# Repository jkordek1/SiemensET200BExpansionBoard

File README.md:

# SiemensET200BExpansionBoard

## Description
PCB expansion device containing 16 SPDT switches for configuring Siemens ET200B.
## Images

## BOM
| #  | QTY | Component | Link
| ------------- | ------------- | ------------- | ------------- |
| 1  | 16 | EG1271A SPDT switch  | [Digikey](https://www.digikey.com/en/products/detail/e-switch/EG1271A/251336) |
| 2  | 1 | 5.08mm 1x2 screw terminal  | [Digikey](https://www.digikey.com/en/products/detail/cui-devices/TB006-508-02BE/10064115) |

## Project folder structure
    .
    ├── ...
    ├── Images                  # Images of the project
    ├── KiCAD Files             # Main folder
    │   ├── 3D                  # 3D models of added components
    │   ├── Images              # Graphics added to silk
    │   └── jlcpcb              # gerber and assembly folder - addon
    └── ...

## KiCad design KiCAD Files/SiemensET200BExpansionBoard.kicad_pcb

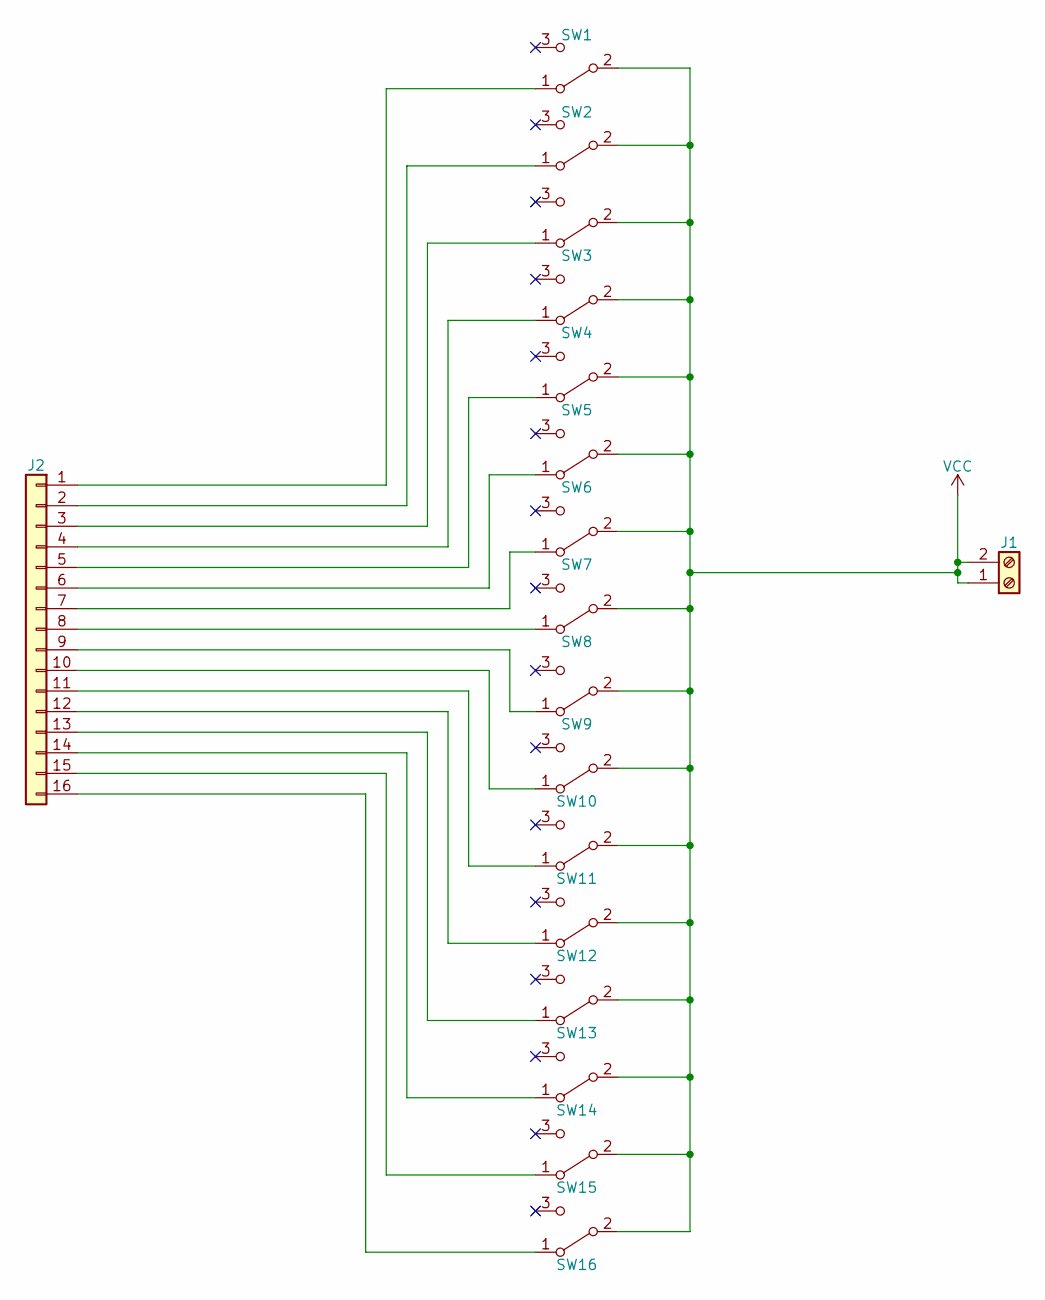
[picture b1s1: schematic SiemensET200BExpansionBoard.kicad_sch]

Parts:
J1: Screw_Terminal_01x02; TerminalBlock_Phoenix_MKDS-1,5-2-5.08_1x02_P5.08mm_Horizont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
J2: Conn_01x16; Konektor
SW1, SW2, SW3, SW4, SW5, SW6, SW7, SW8, SW9, SW10, SW11, SW12, SW13, SW14, SW15, SW16: SW_SPDT; EG1271A

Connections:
unnamed: J2.1, SW1.1 (A)
unnamed: J2.2, SW2.1 (A)
unnamed: J2.3, SW3.1 (A)
unnamed: J2.4, SW4.1 (A)
unnamed: J2.5, SW5.1 (A)
unnamed: J2.6, SW6.1 (A)
unnamed: J2.7, SW7.1 (A)
unnamed: J2.8, SW8.1 (A)
unnamed: J2.9, SW9.1 (A)
unnamed: J2.10, SW10.1 (A)
unnamed: J2.11, SW11.1 (A)
unnamed: J2.12, SW12.1 (A)
unnamed: J2.13, SW13.1 (A)
unnamed: J2.14, SW14.1 (A)
unnamed: J2.15, SW15.1 (A)
unnamed: J2.16, SW16.1 (A)
VCC: J1.1, J1.2, SW1.2 (B), SW2.2 (B), SW3.2 (B), SW4.2 (B), SW5.2 (B), SW6.2 (B), SW7.2 (B), SW8.2 (B), SW9.2 (B), SW10.2 (B), SW11.2 (B), SW12.2 (B), SW13.2 (B), SW14.2 (B), SW15.2 (B), SW16.2 (B)

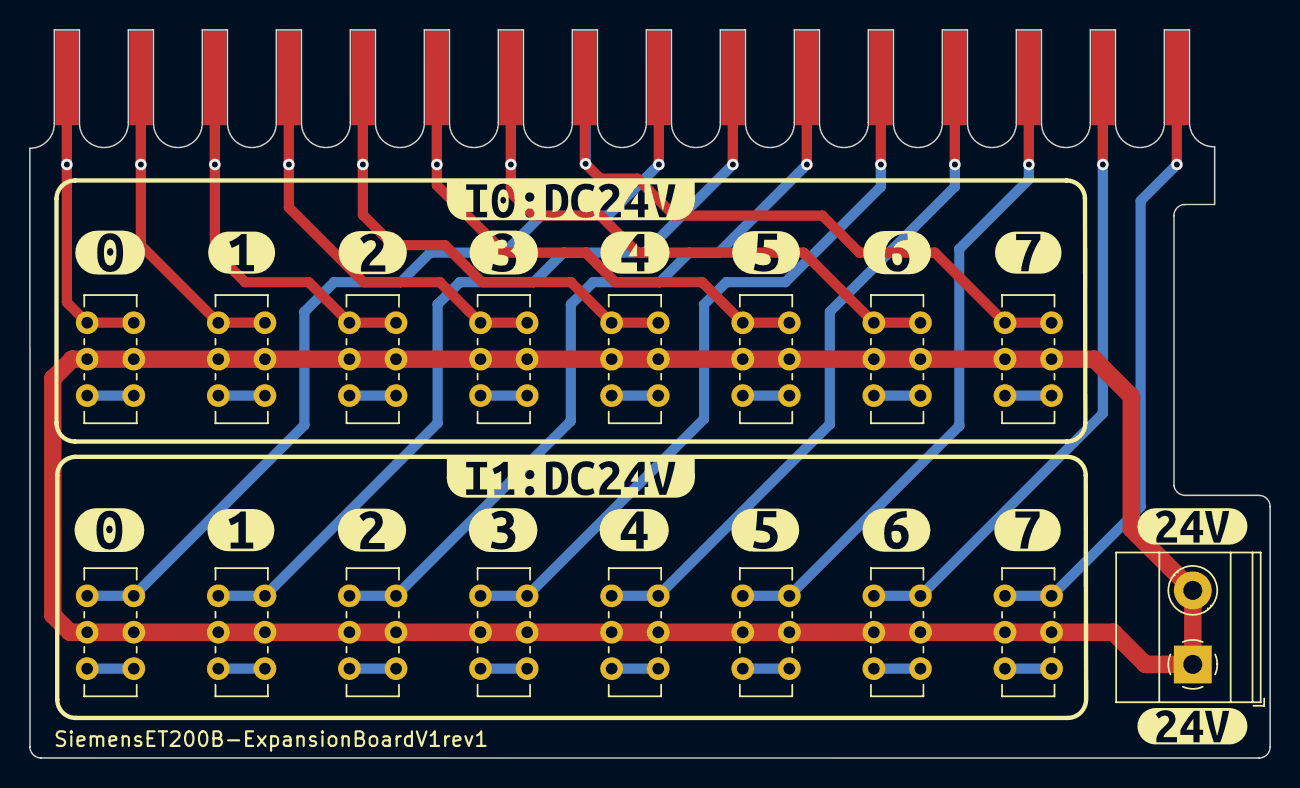
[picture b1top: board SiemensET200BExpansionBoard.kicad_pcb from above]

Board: 2 copper layers, 85.1 x 50.0 mm, 38 parts (0 on the bottom side), 17 nets.

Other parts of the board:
kibuzzard-63C10C4F, kibuzzard-63C10C4F#2: G***; kibuzzard-63C10C4F
kibuzzard-63C11BDD: G***; kibuzzard-63C11BDD
kibuzzard-63C11C3D: G***; kibuzzard-63C11C3D
kibuzzard-63C11C89, kibuzzard-63C11C89#2: G***; kibuzzard-63C11C89
kibuzzard-63C11C98, kibuzzard-63C11C98#2: G***; kibuzzard-63C11C98
kibuzzard-63C11CB4, kibuzzard-63C11CB4#2: G***; kibuzzard-63C11CB4
kibuzzard-63C11CBB, kibuzzard-63C11CBB#2: G***; kibuzzard-63C11CBB
kibuzzard-63C11CC1, kibuzzard-63C11CC1#2: G***; kibuzzard-63C11CC1
kibuzzard-63C11CC9, kibuzzard-63C11CC9#2: G***; kibuzzard-63C11CC9
kibuzzard-63C11CDA, kibuzzard-63C11CDA#2: G***; kibuzzard-63C11CDA
kibuzzard-63C11CE2, kibuzzard-63C11CE2#2: G***; kibuzzard-63C11CE2

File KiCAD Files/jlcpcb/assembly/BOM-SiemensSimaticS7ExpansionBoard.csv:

Comment,Designator,Footprint,LCSC
SW_SPDT,SW16,EG1271A,
SW_SPDT,SW15,EG1271A,
SW_SPDT,SW14,EG1271A,
SW_SPDT,SW13,EG1271A,
SW_SPDT,SW12,EG1271A,
SW_SPDT,SW11,EG1271A,
SW_SPDT,SW10,EG1271A,
SW_SPDT,SW9,EG1271A,
SW_SPDT,SW8,EG1271A,
SW_SPDT,SW7,EG1271A,
SW_SPDT,SW6,EG1271A,
SW_SPDT,SW5,EG1271A,
SW_SPDT,SW4,EG1271A,
SW_SPDT,SW3,EG1271A,
SW_SPDT,SW2,EG1271A,
SW_SPDT,SW1,EG1271A,
Screw_Terminal_01x02,J1,"TerminalBlock_Phoenix_MKDS-1,5-2-5.08_1x02_P5.08mm_Horizontal",
Conn_01x16,J2,Konektor,

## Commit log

2023-01-13 Initial release
2023-01-13 Add qrcode
2023-02-21 Images
2023-02-21 Resized images
